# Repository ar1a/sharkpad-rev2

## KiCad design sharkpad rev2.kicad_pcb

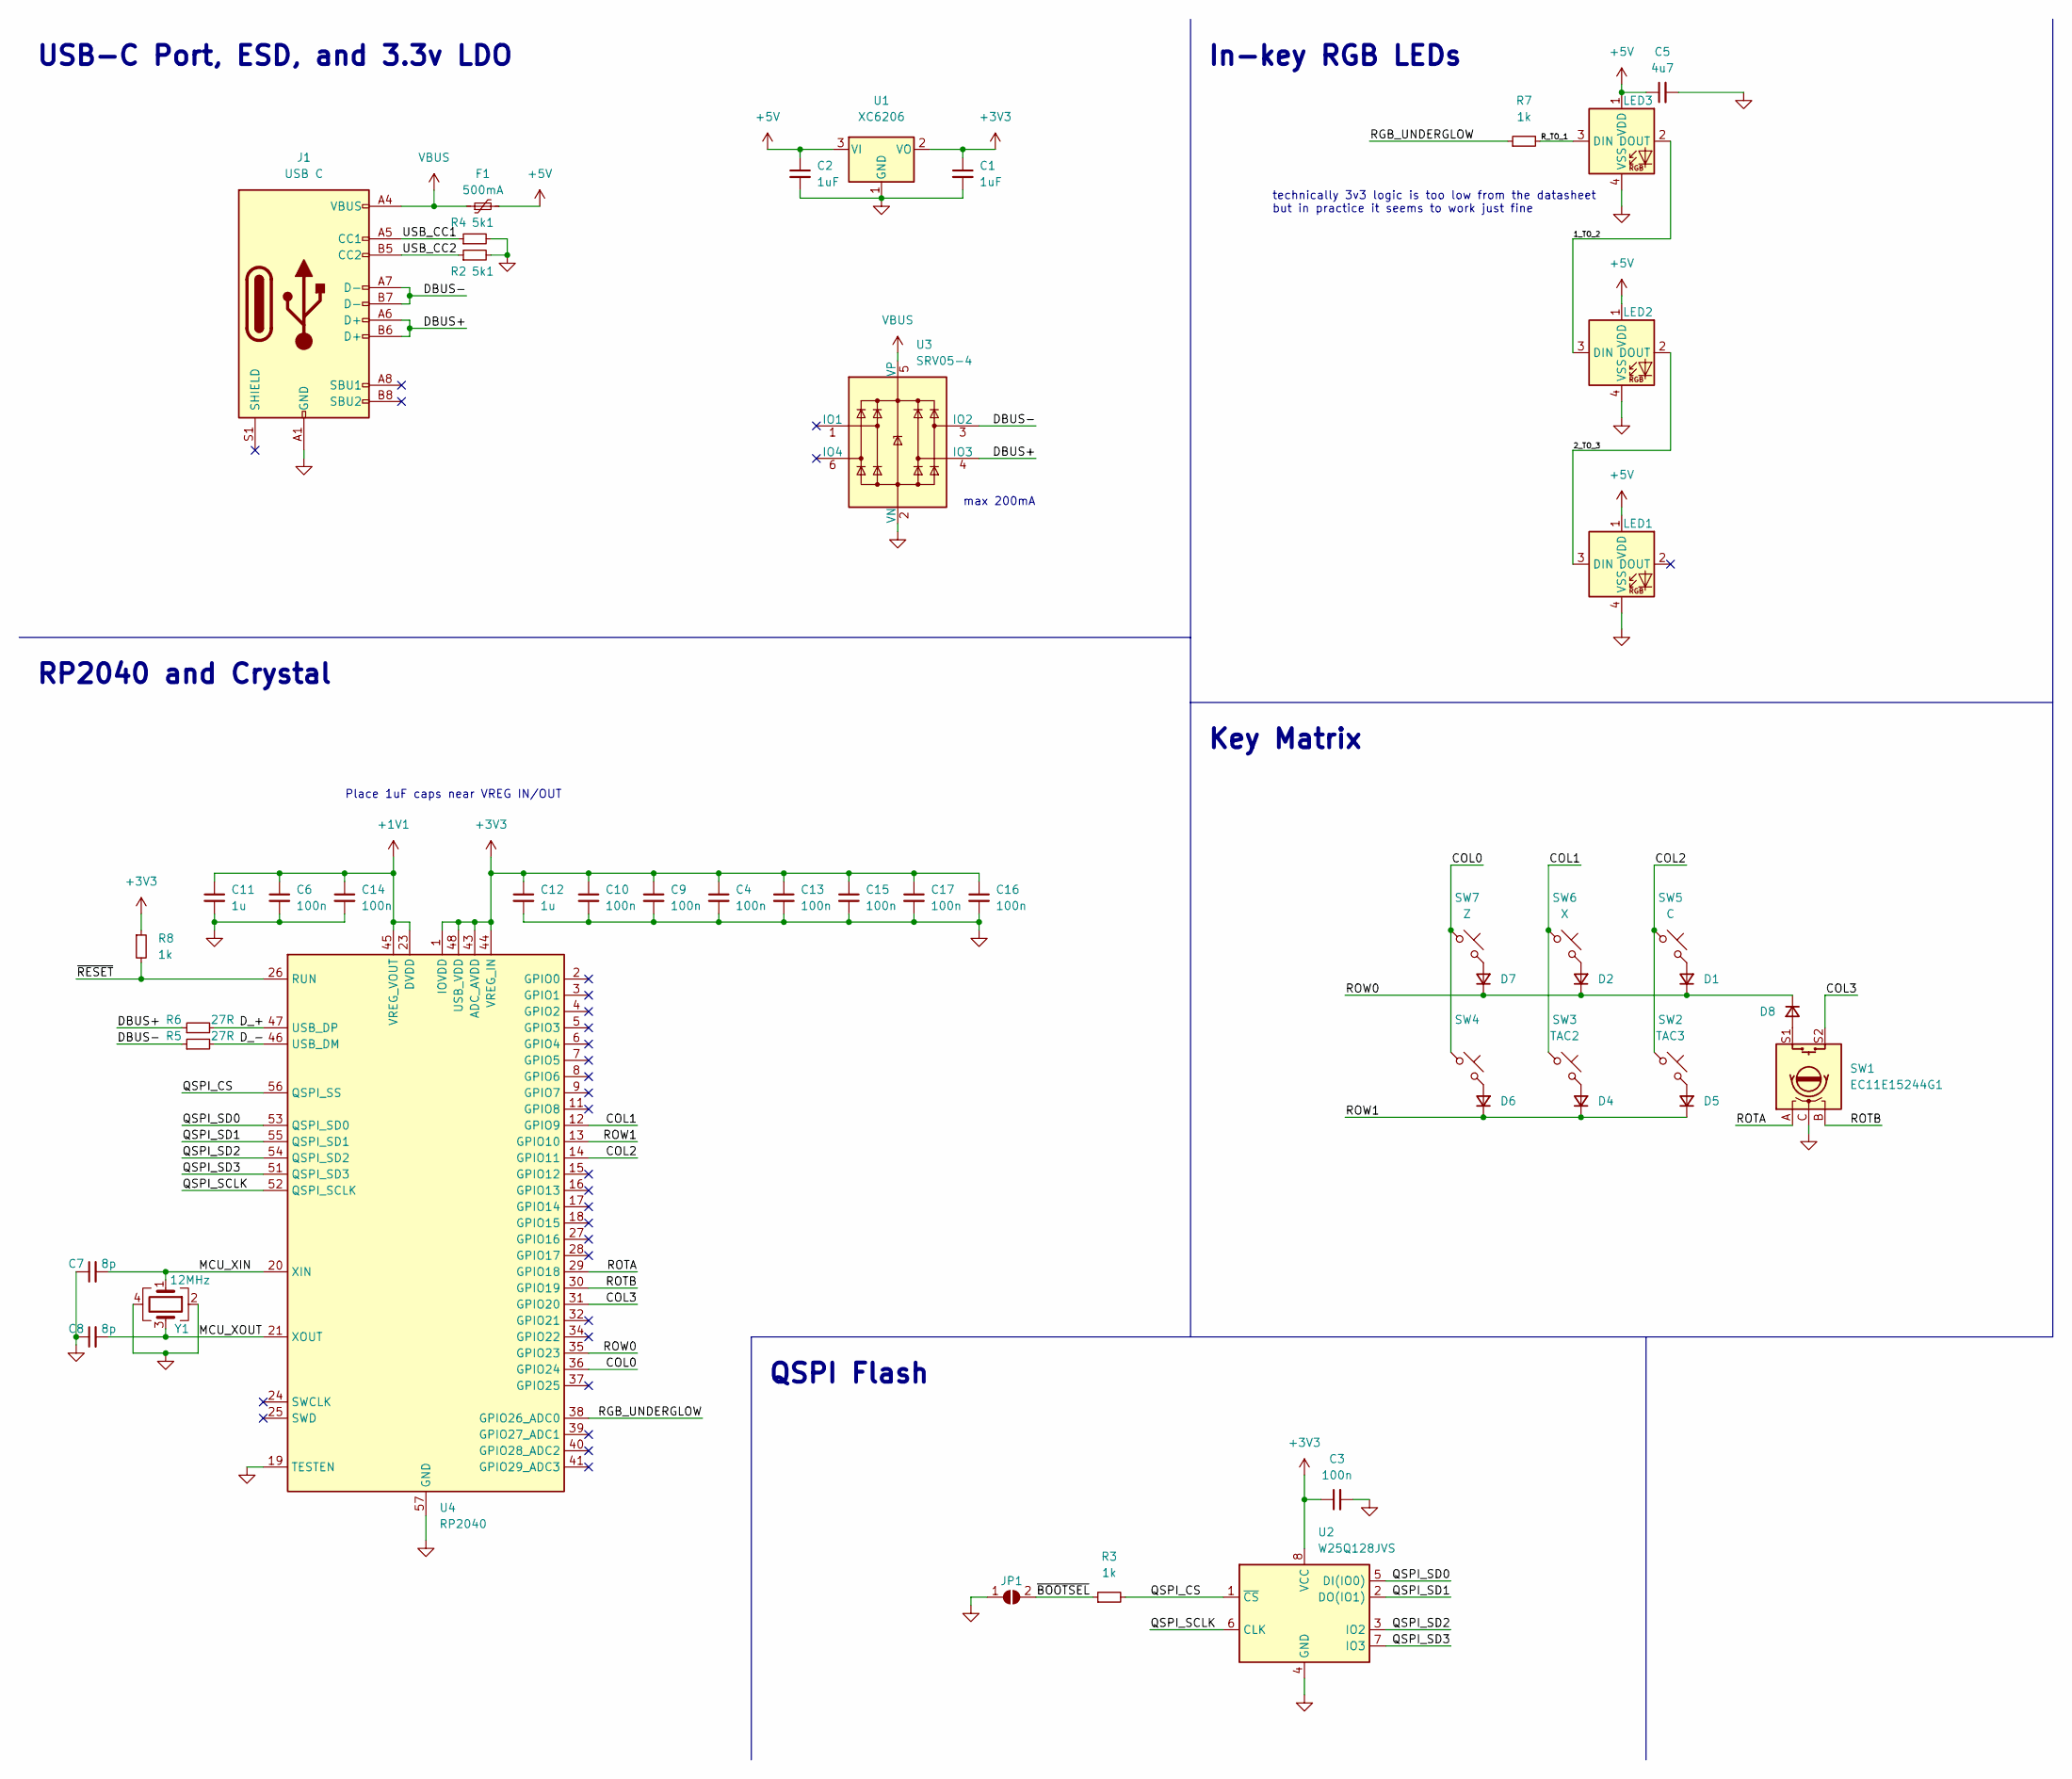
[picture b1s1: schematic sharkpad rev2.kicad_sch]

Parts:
C1, C2: 1uF; C_0402_1005Metric; LCSC C52923
C3, C4, C6, C9, C10, C13, C14, C15, C16, C17: 100n; C_0402_1005Metric; LCSC C307331
C5: 4u7; C_0805_2012Metric; LCSC C1779
C7, C8: 8p; C_0402_1005Metric; LCSC C1578
C11, C12: 1u; C_0402_1005Metric; LCSC C52923
D1, D2, D4, D5, D6, D7, D8: D_Small; D_SOD-123; LCSC C81598
F1: 500mA; Fuse_1206_3216Metric; LCSC C883126
J1: USB C; USB_C_Receptacle_HRO_TYPE-C-31-M-12; LCSC C165948
JP1: BOOTSEL; SW_SPST_SKQG_WithStem
LED1, LED2, LED3: SK6812MINI-E; LED_MX_6028R-FLIPPED; LCSC C5149201
R2, R4: 5k1; R_0402_1005Metric; LCSC C25905
R3, R7, R8: 1k; R_0402_1005Metric; LCSC C11702
R5, R6: 27R; R_0402_1005Metric; LCSC C25100
SW1: EC11E15244G1; ROT_Alps_EC11E-Switch
SW2: TAC3; SW_PUSH_6mm_H13mm
SW3: TAC2; SW_PUSH_6mm_H13mm
SW4: TAC1; SW_PUSH_6mm_H13mm
SW5: C; SW_MX_HS_1u
SW6: X; SW_MX_HS_1u
SW7: Z; SW_MX_HS_1u
U1: XC6206; SOT-23; LCSC C5446
U2: W25Q128JVS; SOIC-8_5.23x5.23mm_P1.27mm; LCSC C97521
U3: SRV05-4; SOT-23-6-routable; LCSC C85364
U4: RP2040; QFN-56-1EP_7x7mm_P0.4mm_EP3.2x3.2mm_ThermalVias; LCSC C2040
Y1: 12MHz; Crystal_SMD_3225-4Pin_3.2x2.5mm; LCSC C9002

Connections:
+1V1: C6.1, C11.1, C14.1, U4.23 (DVDD), U4.45 (VREG_VOUT), U4.50 (DVDD)
+3V3: C1.1, C3.1, C4.1, C9.1, C10.1, C12.1, C13.1, C15.1, C16.1, C17.1, R8.1, U1.2 (VO), U2.8 (VCC), U4.1 (IOVDD), U4.10 (IOVDD), U4.22 (IOVDD), U4.33 (IOVDD), U4.42 (IOVDD), U4.43 (ADC_AVDD), U4.44 (VREG_IN), U4.48 (USB_VDD), U4.49 (IOVDD)
+5V: C2.1, C5.1, F1.2, LED1.1 (VDD), LED2.1 (VDD), LED3.1 (VDD), U1.3 (VI)
/1_TO_2: LED2.3 (DIN), LED3.2 (DOUT)
/2_TO_3: LED1.3 (DIN), LED2.2 (DOUT)
/COL0: SW4.1, SW7.1, U4.36 (GPIO24)
/COL1: SW3.1, SW6.1, U4.12 (GPIO9)
/COL2: SW2.1, SW5.1, U4.14 (GPIO11)
/COL3: SW1.S2, U4.31 (GPIO20)
/DBUS+: J1.A6 (D+), J1.B6 (D+), R6.1, U3.4 (IO3)
/DBUS-: J1.A7 (D-), J1.B7 (D-), R5.1, U3.3 (IO2)
/D_+: R6.2, U4.47 (USB_DP)
/D_-: R5.2, U4.46 (USB_DM)
/MCU_XIN: C7.2, U4.20 (XIN), Y1.1
/QSPI_CS: R3.2, U2.1 (~CS), U4.56 (QSPI_SS)
/QSPI_SCLK: U2.6 (CLK), U4.52 (QSPI_SCLK)
/QSPI_SD0: U2.5 (DI(IO0)), U4.53 (QSPI_SD0)
/QSPI_SD1: U2.2 (DO(IO1)), U4.55 (QSPI_SD1)
/QSPI_SD2: U2.3 (IO2), U4.54 (QSPI_SD2)
/QSPI_SD3: U2.7 (IO3), U4.51 (QSPI_SD3)
/RGB_UNDERGLOW: R7.1, U4.38 (GPIO26_ADC0)
/ROTA: SW1.A, U4.29 (GPIO18)
/ROTB: SW1.B, U4.30 (GPIO19)
/ROW0: D1.1 (K), D2.1 (K), D7.1 (K), D8.1 (K), U4.35 (GPIO23)
/ROW1: D4.1 (K), D5.1 (K), D6.1 (K), U4.13 (GPIO10)
/R_TO_1: LED3.3 (DIN), R7.2
/USB_CC1: J1.A5 (CC1), R4.1
/USB_CC2: J1.B5 (CC2), R2.1
/~BOOTSEL: JP1.2 (B), R3.1
/~RESET: R8.2, U4.26 (RUN)
unnamed: D1.2 (A), SW5.2
unnamed: D2.2 (A), SW6.2
unnamed: D4.2 (A), SW3.2
unnamed: D5.2 (A), SW2.2
unnamed: D6.2 (A), SW4.2
unnamed: D7.2 (A), SW7.2
unnamed: D8.2 (A), SW1.S1
VBUS: F1.1, J1.A4 (VBUS), J1.A9 (VBUS), J1.B4 (VBUS), J1.B9 (VBUS), U3.5 (VP)

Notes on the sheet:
Key Matrix
USB-C Port, ESD, and 3.3v LDO
QSPI Flash
technically 3v3 logic is too low from the datasheet but in practice it seems to work just fine
In-key RGB LEDs
RP2040 and Crystal
Place 1uF caps near VREG IN/OUT
max 200mA

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
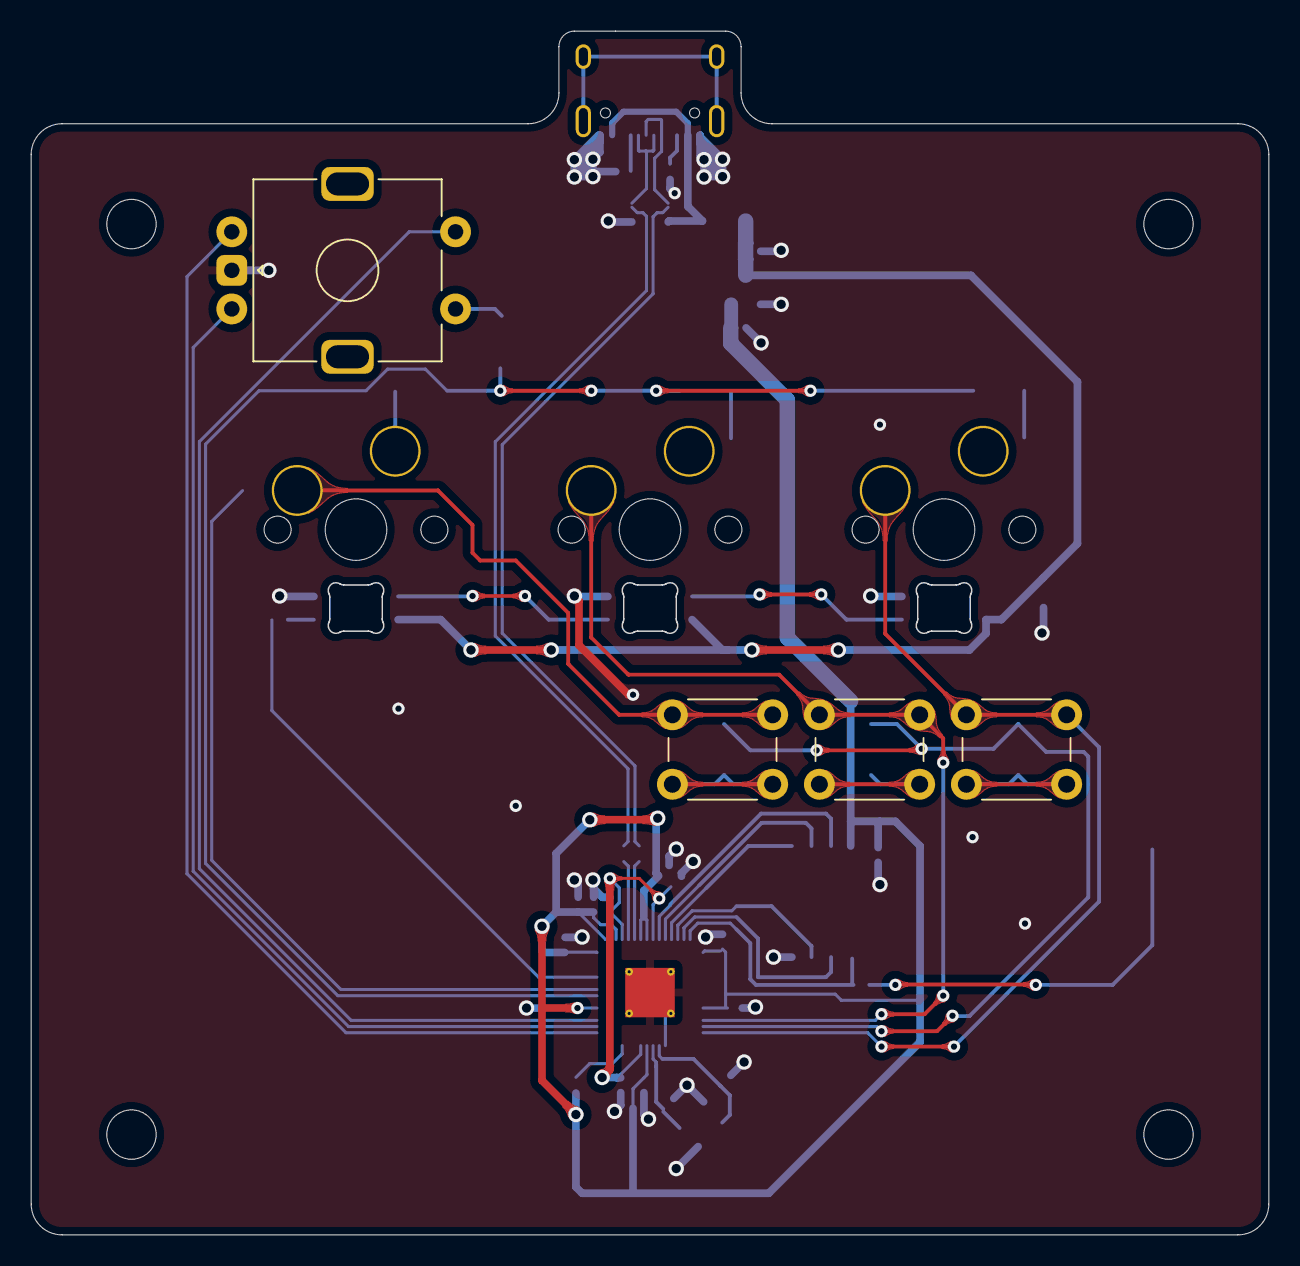
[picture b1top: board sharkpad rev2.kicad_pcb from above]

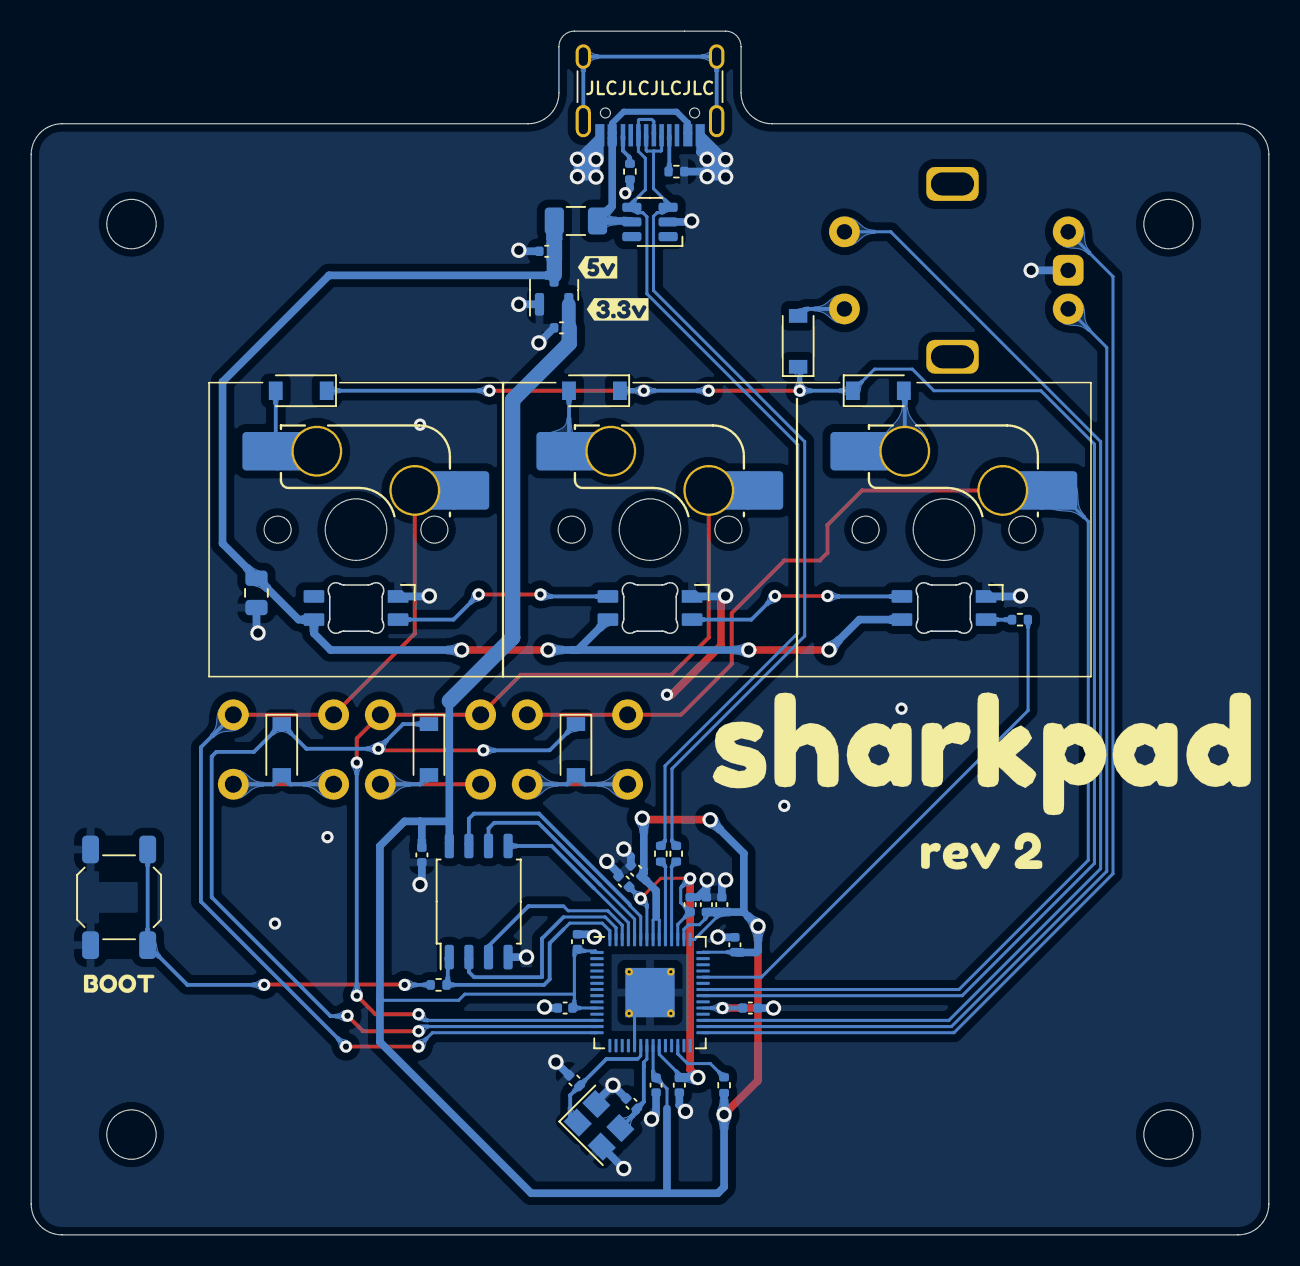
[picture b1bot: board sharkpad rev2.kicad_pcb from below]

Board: 2 copper layers, 80.1 x 77.9 mm, 54 parts (50 on the bottom side), 40 nets.

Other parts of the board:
kibuzzard-1: G***; kibuzzard-638A2CDC
kibuzzard-2: G***; kibuzzard-638A2C3F
kibuzzard-3: G***; kibuzzard-638A2C0C
kibuzzard-5: G***; kibuzzard-638B4E2B
kibuzzard-6: G***; kibuzzard-638B4E4E

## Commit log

2022-12-02 init
2022-12-02 Generate gerbers
2022-12-02 remove leds from bom, move jumper to side of board
2022-12-03 nothing changes
2022-12-03 rev2 first draft
2022-12-03 rev2 draft 2
2023-04-21 finish
